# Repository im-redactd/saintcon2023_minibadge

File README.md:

# Saintcon 2023 RP2040 Minibadge
 Minibadge Software

 # Flashing

 If you wish to flash your minibadge you'll need to use a Tag-Connect TC2050-IDC-NL cable or rig up your own SWD pins to attach to the footprint.

 I used a JLink EDU Mini.

# Branches

This is the main branch build on the Arduino-MBED core in platformio. The EarleH branch contains the changes needed to run that core if you're interested.

# Debugging
launch.json entry
```
"configurations": [
        {
            "cwd": "${workspaceFolder}",
            "executable": "d:/GDrive/Projects/KiCad/Minibadge/saintcon-rp2040-platform-kicad7/software/saintcon2023_minibadge/.pio/build/pico/firmware.elf",
            "name": "Debug with JLink",
            "request": "launch",
            "type": "cortex-debug",
            "device": "RP2040_M0_0",
            "serverpath": "C:/.platformio/packages/tool-jlink/JLinkGDBServerCL.exe",
            "runToEntryPoint": "main",
            "showDevDebugOutput": "none",
            "servertype": "jlink"
        },
```

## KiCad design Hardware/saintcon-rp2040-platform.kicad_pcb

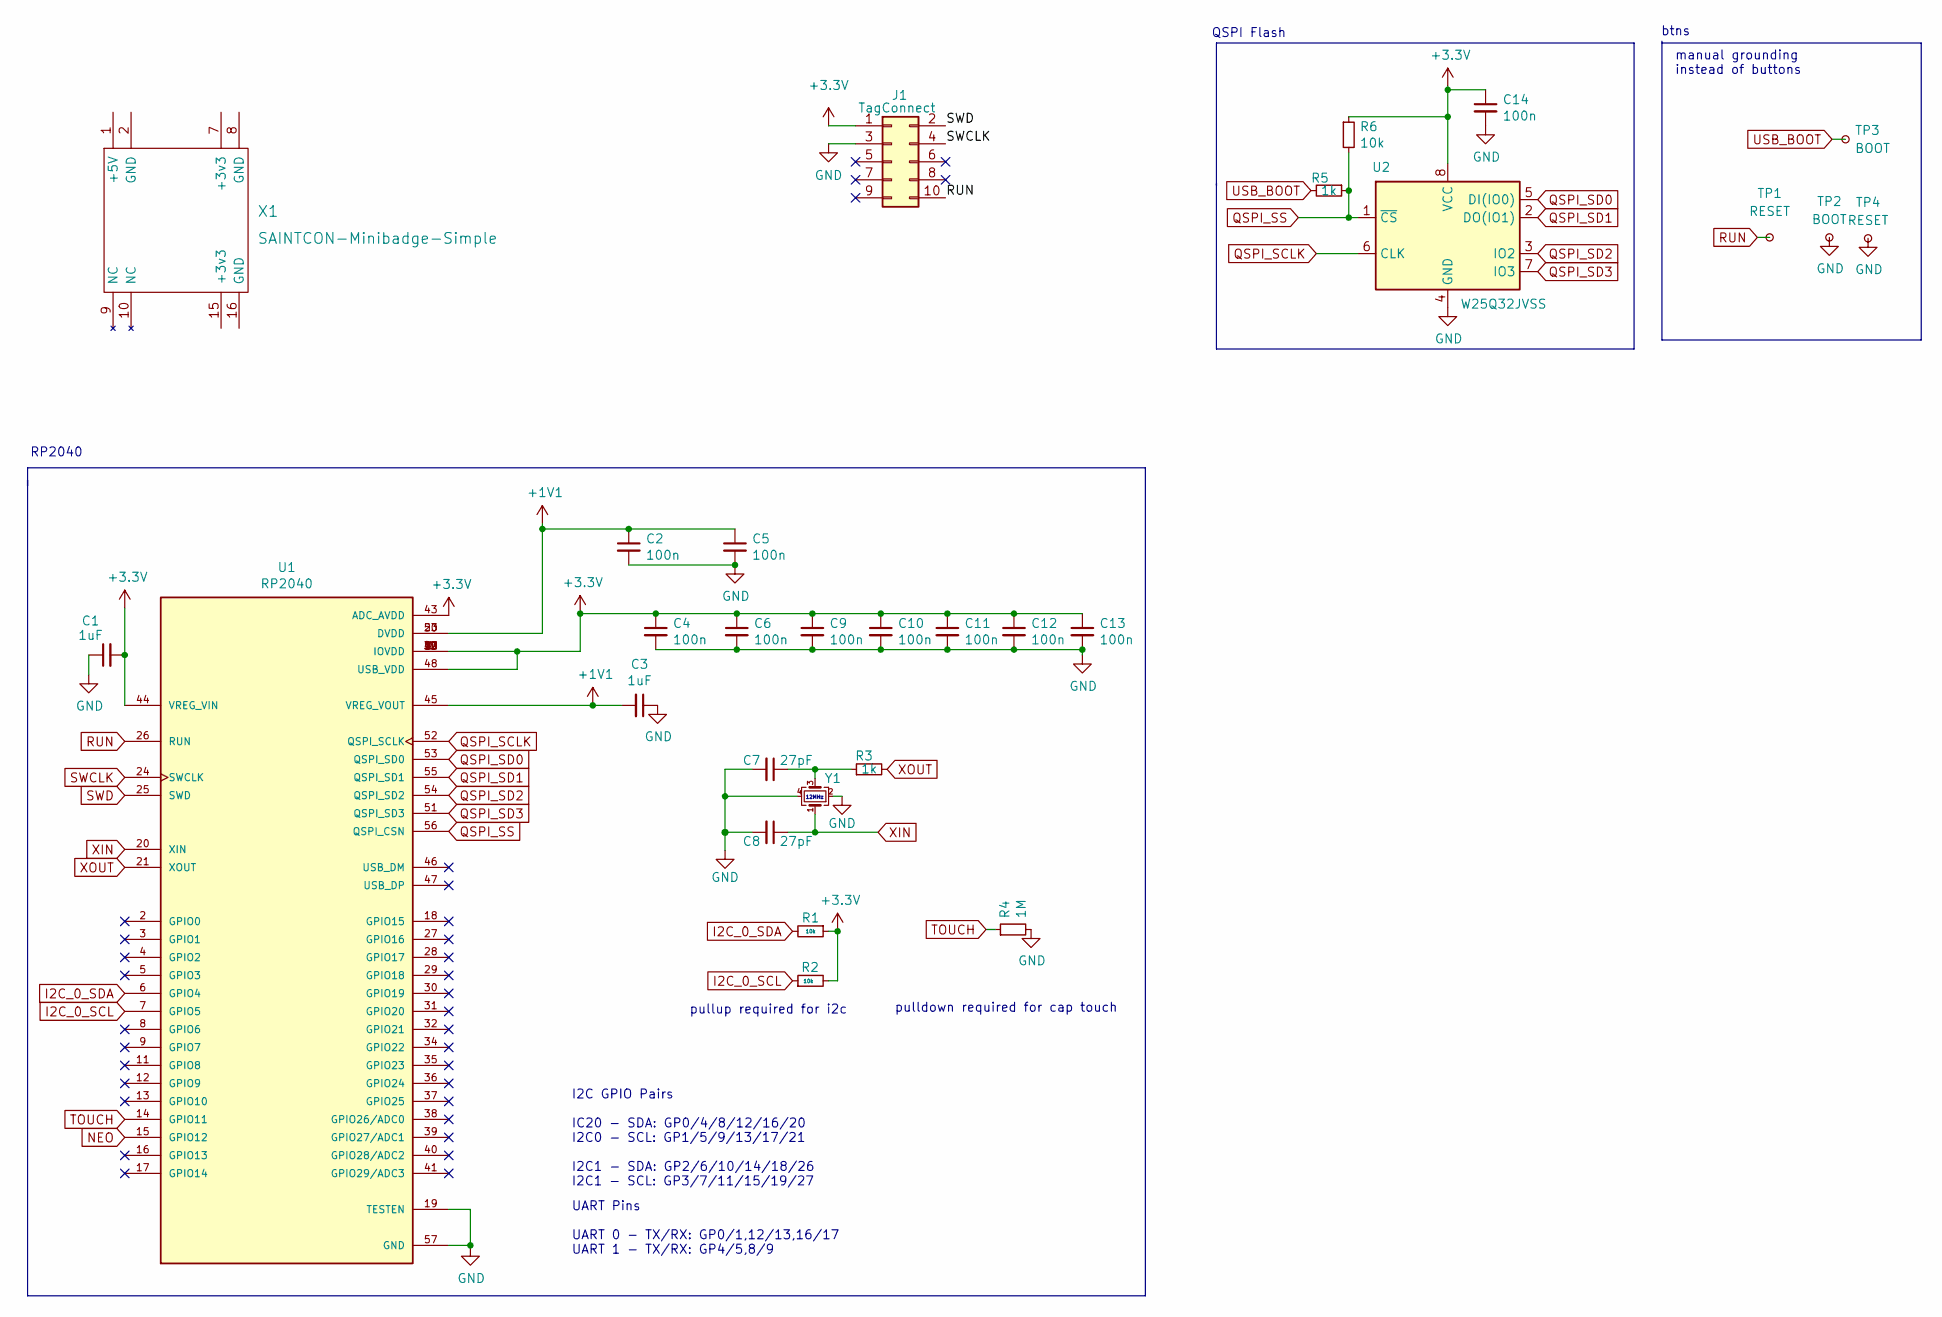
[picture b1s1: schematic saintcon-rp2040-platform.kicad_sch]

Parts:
C1, C3: 1uF; C_0402_1005Metric
C2, C4, C5, C6, C9, C10, C11, C12, C13, C14: 100n; C_0402_1005Metric
C7, C8: 27pF; C_0402_1005Metric
J1: TagConnect; TAG-CONNECT_TC2050-IDC-NL
R1, R2, R6: 10k; R_0402_1005Metric
R3, R5: 1k; R_0402_1005Metric
R4: 1M; R_0402_1005Metric
TP1, TP4: RESET; TestPoint_Pad_1.0x1.0mm
TP2, TP3: BOOT; TestPoint_Pad_1.0x1.0mm
U1: RP2040; QFN40P700X700X90-57N; PARTREV 1.6.1
U2: W25Q32JVSS; W25Q16JVUXIQ_WIN-L
X1: SAINTCON-Minibadge-Simple; SAINTCON-Minibadge-redactd2023
Y1: ECS-120-18-33-JGN-TR; Crystal_SMD_2520-4Pin_2.5x2.0mm; DigiKey XC2300TR-ND

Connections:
+1V1: C2.1, C3.2, C5.1, U1.23 (DVDD), U1.45 (VREG_VOUT), U1.50 (DVDD)
+3V3: C1.2, C4.1, C6.1, C9.1, C10.1, C11.1, C12.1, C13.1, C14.1, J1.1, R1.1, R2.2, R6.1, U1.1 (IOVDD), U1.10 (IOVDD), U1.22 (IOVDD), U1.33 (IOVDD), U1.42 (IOVDD), U1.43 (ADC_AVDD), U1.44 (VREG_VIN), U1.48 (USB_VDD), U1.49 (IOVDD), U2.8 (VCC), X1.7 (+3v3), X1.15 (+3v3)
GND: C1.1, C2.2, C3.1, C4.2, C5.2, C6.2, C7.2, C8.2, C9.2, C10.2, C11.2, C12.2, C13.2, C14.2, J1.3, R4.2, TP2.1, TP4.1, U1.19 (TESTEN), U1.57 (GND), U2.4 (GND), X1.2 (GND), X1.8 (GND), X1.16 (GND), Y1.2, Y1.4
I2C_0_SCL: R2.1, U1.7 (GPIO5), X1.13
I2C_0_SDA: R1.2, U1.6 (GPIO4), X1.14
NEO: U1.15 (GPIO12), X1.10 (NC)
unnamed: C7.1, R3.1, Y1.3
QSPI_SCLK: U1.52 (QSPI_SCLK), U2.6 (CLK)
QSPI_SD0: U1.53 (QSPI_SD0), U2.5 (DI(IO0))
QSPI_SD1: U1.55 (QSPI_SD1), U2.2 (DO(IO1))
QSPI_SD2: U1.54 (QSPI_SD2), U2.3 (IO2)
QSPI_SD3: U1.51 (QSPI_SD3), U2.7 (IO3)
QSPI_SS: R5.1, R6.2, U1.56 (QSPI_CSN), U2.1 (~CS)
RUN: J1.10, TP1.1, U1.26 (RUN)
SWCLK: J1.4, U1.24 (SWCLK)
SWD: J1.2, U1.25 (SWD)
TOUCH: R4.1, U1.14 (GPIO11), X1.9 (NC)
USB_BOOT: R5.2, TP3.1
XIN: C8.1, U1.20 (XIN), Y1.1
XOUT: R3.2, U1.21 (XOUT)

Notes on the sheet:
manual grounding instead of buttons
btns
I2C GPIO Pairs IC20 - SDA: GP0/4/8/12/16/20 I2C0 - SCL: GP1/5/9/13/17/21 I2C1 - SDA: GP2/6/10/14/18/26 I2C1 - SCL: GP3/7/11/15/19/27
RP2040
pullup required for i2c
UART Pins UART 0 - TX/RX: GP0/1,12/13,16/17 UART 1 - TX/RX: GP4/5,8/9
QSPI Flash
12MHz
pulldown required for cap touch

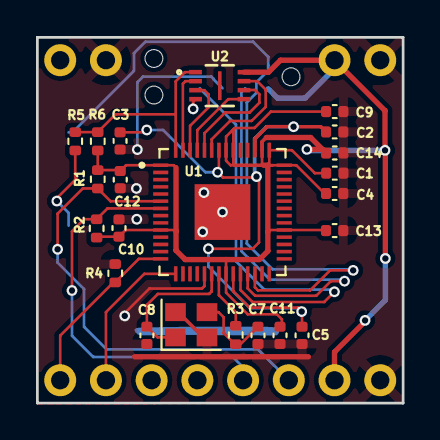
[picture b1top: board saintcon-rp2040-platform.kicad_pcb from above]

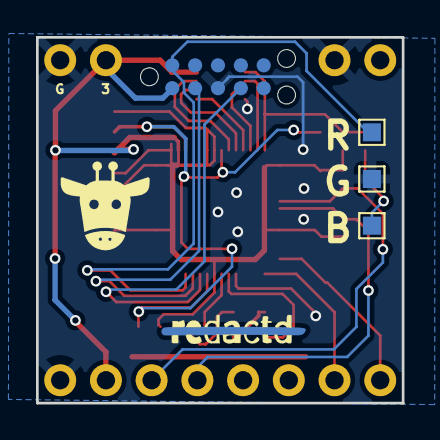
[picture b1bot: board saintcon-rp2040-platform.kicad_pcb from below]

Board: 2 copper layers, 20.3 x 20.3 mm, 28 parts (5 on the bottom side), 20 nets.

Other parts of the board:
Ref**: Val**; redactd_copper_strike_v1_8mm

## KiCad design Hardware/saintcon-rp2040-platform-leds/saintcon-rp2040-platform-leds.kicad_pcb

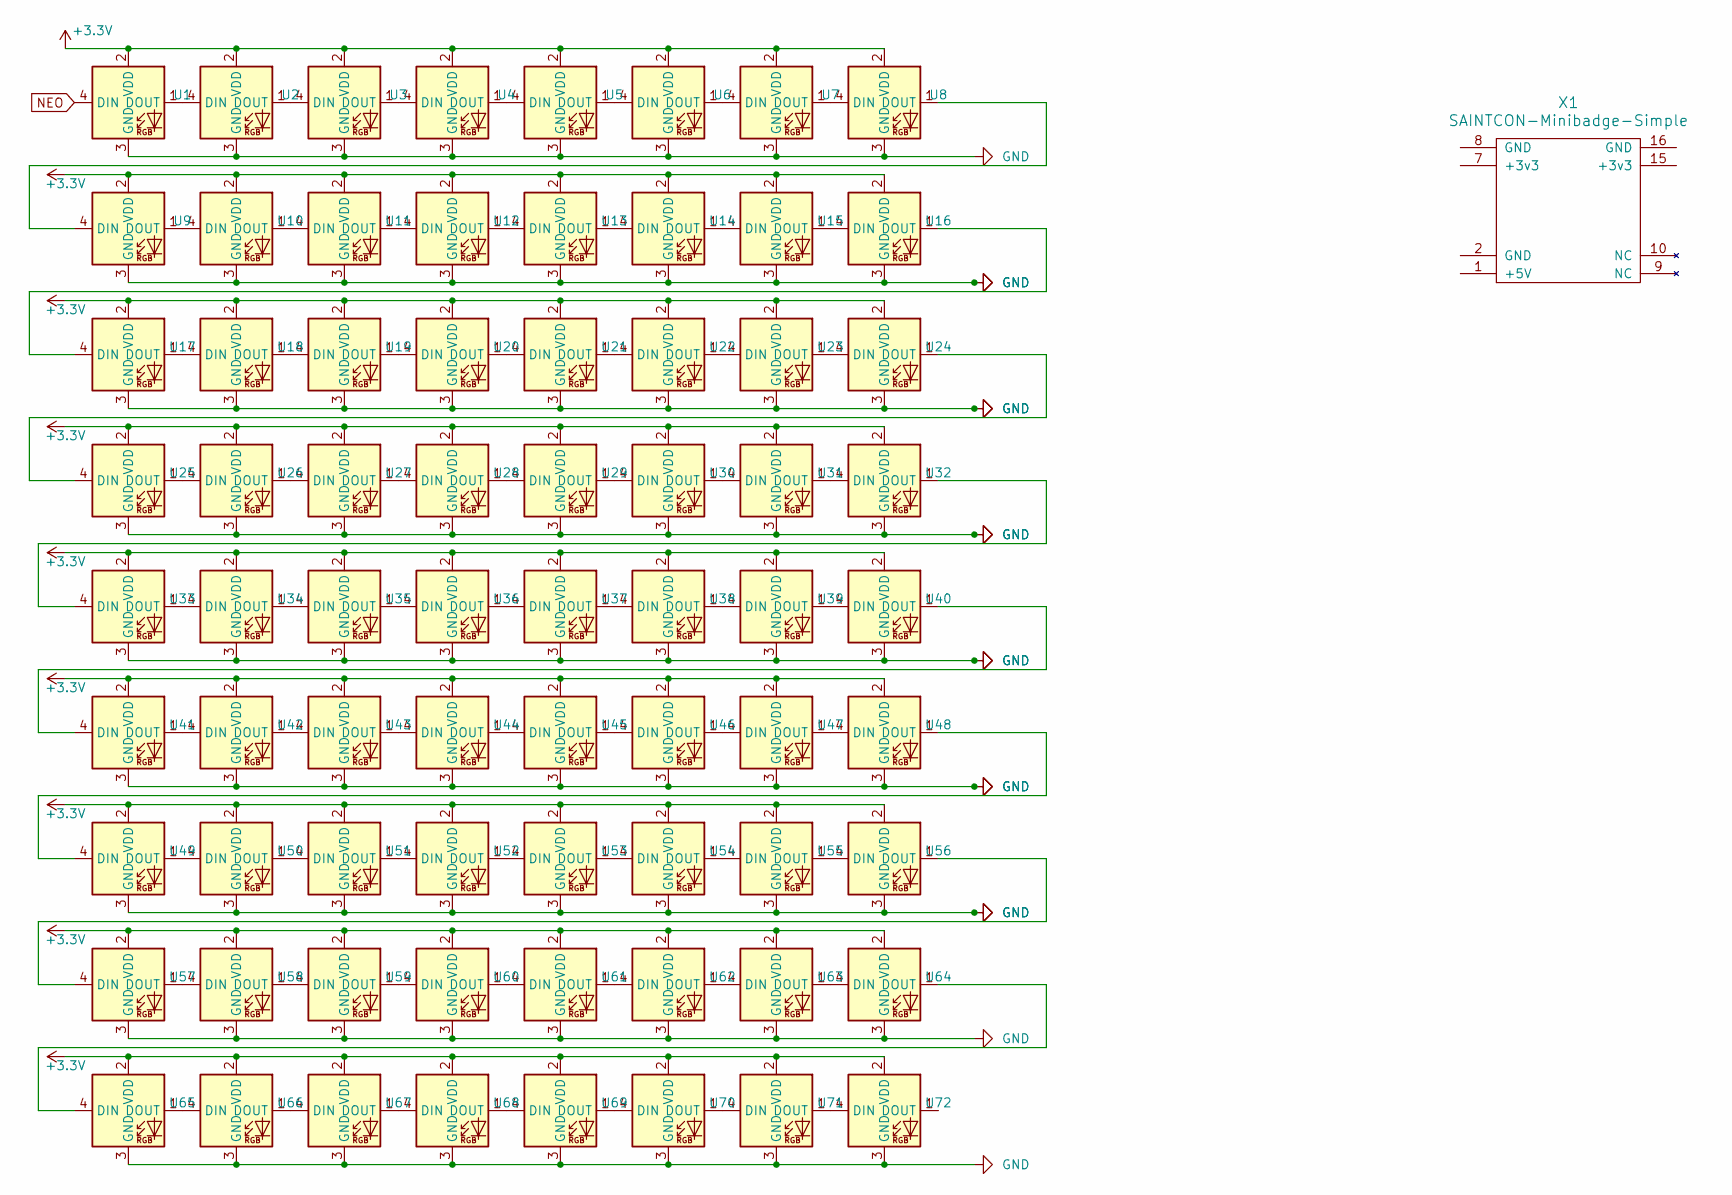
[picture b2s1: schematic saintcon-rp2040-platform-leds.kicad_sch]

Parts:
U1, U2, U3, U4, U5, U6, U7, U8, U9, U10, U11, U12, U13, U14, U15, U16, U17, U18, U19, U20, U21, U22, U23, U24, U25, U26, U27, U28, U29, U30, U31, U32, U33, U34, U35, U36, U37, U38, U39, U40, U41, U42, U43, U44, U45, U46, U47, U48, U49, U50, U51, U52, U53, U54, U55, U56, U57, U58, U59, U60, U61, U62, U63, U64, U65, U66, U67, U68, U69, U70, U71, U72: XINGLIGHT-XL-1010RGBC-WS2812B
X1: SAINTCON-Minibadge-Simple; SAINTCON-Minibadge-redactd2023-top

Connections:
+3.3V: U1.2 (VDD), U2.2 (VDD), U3.2 (VDD), U4.2 (VDD), U5.2 (VDD), U6.2 (VDD), U7.2 (VDD), U8.2 (VDD), U9.2 (VDD), U10.2 (VDD), U11.2 (VDD), U12.2 (VDD), U13.2 (VDD), U14.2 (VDD), U15.2 (VDD), U16.2 (VDD), U17.2 (VDD), U18.2 (VDD), U19.2 (VDD), U20.2 (VDD), U21.2 (VDD), U22.2 (VDD), U23.2 (VDD), U24.2 (VDD), U25.2 (VDD), U26.2 (VDD), U27.2 (VDD), U28.2 (VDD), U29.2 (VDD), U30.2 (VDD), U31.2 (VDD), U32.2 (VDD), U33.2 (VDD), U34.2 (VDD), U35.2 (VDD), U36.2 (VDD), U37.2 (VDD), U38.2 (VDD), U39.2 (VDD), U40.2 (VDD), U41.2 (VDD), U42.2 (VDD), U43.2 (VDD), U44.2 (VDD), U45.2 (VDD), U46.2 (VDD), U47.2 (VDD), U48.2 (VDD), U49.2 (VDD), U50.2 (VDD), U51.2 (VDD), U52.2 (VDD), U53.2 (VDD), U54.2 (VDD), U55.2 (VDD), U56.2 (VDD), U57.2 (VDD), U58.2 (VDD), U59.2 (VDD), U60.2 (VDD), U61.2 (VDD), U62.2 (VDD), U63.2 (VDD), U64.2 (VDD), U65.2 (VDD), U66.2 (VDD), U67.2 (VDD), U68.2 (VDD), U69.2 (VDD), U70.2 (VDD), U71.2 (VDD), U72.2 (VDD), X1.7 (+3v3), X1.15 (+3v3)
GND: U1.3 (GND), U2.3 (GND), U3.3 (GND), U4.3 (GND), U5.3 (GND), U6.3 (GND), U7.3 (GND), U8.3 (GND), U9.3 (GND), U10.3 (GND), U11.3 (GND), U12.3 (GND), U13.3 (GND), U14.3 (GND), U15.3 (GND), U16.3 (GND), U17.3 (GND), U18.3 (GND), U19.3 (GND), U20.3 (GND), U21.3 (GND), U22.3 (GND), U23.3 (GND), U24.3 (GND), U25.3 (GND), U26.3 (GND), U27.3 (GND), U28.3 (GND), U29.3 (GND), U30.3 (GND), U31.3 (GND), U32.3 (GND), U33.3 (GND), U34.3 (GND), U35.3 (GND), U36.3 (GND), U37.3 (GND), U38.3 (GND), U39.3 (GND), U40.3 (GND), U41.3 (GND), U42.3 (GND), U43.3 (GND), U44.3 (GND), U45.3 (GND), U46.3 (GND), U47.3 (GND), U48.3 (GND), U49.3 (GND), U50.3 (GND), U51.3 (GND), U52.3 (GND), U53.3 (GND), U54.3 (GND), U55.3 (GND), U56.3 (GND), U57.3 (GND), U58.3 (GND), U59.3 (GND), U60.3 (GND), U61.3 (GND), U62.3 (GND), U63.3 (GND), U64.3 (GND), U65.3 (GND), U66.3 (GND), U67.3 (GND), U68.3 (GND), U69.3 (GND), U70.3 (GND), U71.3 (GND), U72.3 (GND), X1.2 (GND), X1.8 (GND), X1.16 (GND)
NEO: U1.4 (DIN), X1.10 (NC)
unnamed: U1.1 (DOUT), U2.4 (DIN)
unnamed: U2.1 (DOUT), U3.4 (DIN)
unnamed: U3.1 (DOUT), U4.4 (DIN)
unnamed: U4.1 (DOUT), U5.4 (DIN)
unnamed: U5.1 (DOUT), U6.4 (DIN)
unnamed: U6.1 (DOUT), U7.4 (DIN)
unnamed: U7.1 (DOUT), U8.4 (DIN)
unnamed: U8.1 (DOUT), U9.4 (DIN)
unnamed: U9.1 (DOUT), U10.4 (DIN)
unnamed: U10.1 (DOUT), U11.4 (DIN)
unnamed: U11.1 (DOUT), U12.4 (DIN)
unnamed: U12.1 (DOUT), U13.4 (DIN)
unnamed: U13.1 (DOUT), U14.4 (DIN)
unnamed: U14.1 (DOUT), U15.4 (DIN)
unnamed: U15.1 (DOUT), U16.4 (DIN)
unnamed: U16.1 (DOUT), U17.4 (DIN)
unnamed: U17.1 (DOUT), U18.4 (DIN)
unnamed: U18.1 (DOUT), U19.4 (DIN)
unnamed: U19.1 (DOUT), U20.4 (DIN)
unnamed: U20.1 (DOUT), U21.4 (DIN)
unnamed: U21.1 (DOUT), U22.4 (DIN)
unnamed: U22.1 (DOUT), U23.4 (DIN)
unnamed: U23.1 (DOUT), U24.4 (DIN)
unnamed: U24.1 (DOUT), U25.4 (DIN)
unnamed: U25.1 (DOUT), U26.4 (DIN)
unnamed: U26.1 (DOUT), U27.4 (DIN)
unnamed: U27.1 (DOUT), U28.4 (DIN)
unnamed: U28.1 (DOUT), U29.4 (DIN)
unnamed: U29.1 (DOUT), U30.4 (DIN)
unnamed: U30.1 (DOUT), U31.4 (DIN)
unnamed: U31.1 (DOUT), U32.4 (DIN)
unnamed: U32.1 (DOUT), U33.4 (DIN)
unnamed: U33.1 (DOUT), U34.4 (DIN)
unnamed: U34.1 (DOUT), U35.4 (DIN)
unnamed: U35.1 (DOUT), U36.4 (DIN)
unnamed: U36.1 (DOUT), U37.4 (DIN)
unnamed: U37.1 (DOUT), U38.4 (DIN)
unnamed: U38.1 (DOUT), U39.4 (DIN)
unnamed: U39.1 (DOUT), U40.4 (DIN)
unnamed: U40.1 (DOUT), U41.4 (DIN)
unnamed: U41.1 (DOUT), U42.4 (DIN)
unnamed: U42.1 (DOUT), U43.4 (DIN)
unnamed: U43.1 (DOUT), U44.4 (DIN)
unnamed: U44.1 (DOUT), U45.4 (DIN)
unnamed: U45.1 (DOUT), U46.4 (DIN)
unnamed: U46.1 (DOUT), U47.4 (DIN)
unnamed: U47.1 (DOUT), U48.4 (DIN)
unnamed: U48.1 (DOUT), U49.4 (DIN)
unnamed: U49.1 (DOUT), U50.4 (DIN)
unnamed: U50.1 (DOUT), U51.4 (DIN)
unnamed: U51.1 (DOUT), U52.4 (DIN)
unnamed: U52.1 (DOUT), U53.4 (DIN)
unnamed: U53.1 (DOUT), U54.4 (DIN)
unnamed: U54.1 (DOUT), U55.4 (DIN)
unnamed: U55.1 (DOUT), U56.4 (DIN)
unnamed: U56.1 (DOUT), U57.4 (DIN)
unnamed: U57.1 (DOUT), U58.4 (DIN)
unnamed: U58.1 (DOUT), U59.4 (DIN)
unnamed: U59.1 (DOUT), U60.4 (DIN)
unnamed: U60.1 (DOUT), U61.4 (DIN)
unnamed: U61.1 (DOUT), U62.4 (DIN)
unnamed: U62.1 (DOUT), U63.4 (DIN)
unnamed: U63.1 (DOUT), U64.4 (DIN)
unnamed: U64.1 (DOUT), U65.4 (DIN)
unnamed: U65.1 (DOUT), U66.4 (DIN)
unnamed: U66.1 (DOUT), U67.4 (DIN)
unnamed: U67.1 (DOUT), U68.4 (DIN)
unnamed: U68.1 (DOUT), U69.4 (DIN)
unnamed: U69.1 (DOUT), U70.4 (DIN)
unnamed: U70.1 (DOUT), U71.4 (DIN)
unnamed: U71.1 (DOUT), U72.4 (DIN)

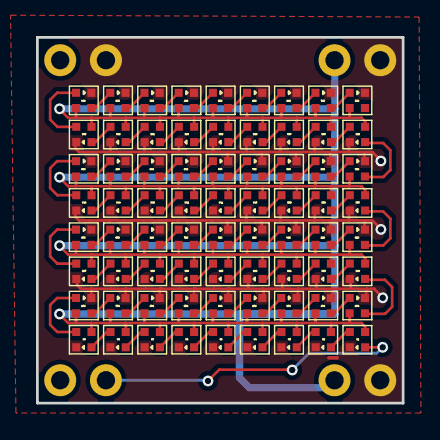
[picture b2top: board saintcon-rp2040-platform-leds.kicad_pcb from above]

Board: 2 copper layers, 20.3 x 20.3 mm, 73 parts (0 on the bottom side), 74 nets.

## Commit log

2023-11-05 Saintcon 2023 Minibadge
2023-11-05 EarleH Core
2023-11-05 about
2023-11-05 Hardware - Kicad
2024-01-24 woops.
